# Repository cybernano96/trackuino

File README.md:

This is a modified version of "Trackuino": an open-source APRS tracker based on the Arduino platform. It was designed primarily to track high altitude balloons, so it has other handy features like reading temperature sensors and a buzzer for acoustic location.

Trackuino is intended for use by licensed radio amateurs.

This modified version supports serial via SoftwareSerial and the DRA818V radio module

**Please note:** This project is a fork of Trackuino, they are the original creators of the code.

Features
========

 * Custom PCB
 * GPS: any NMEA GPS will work fine
 * Radio: DRA818V (500/1000 mW).
 * 1200 bauds AFSK using 8-bit PWM
 * Sends out standard APRS position messages (latitude, longitude, altitude, course, speed and time).
 * Internal/external temperature sensors (LM60) to read temperature in and outside the payload
 * Active/passive buzzer support to ease acoustic payload location.
 * 1 x SMA female plugs (radio out)
 * Open source (GPLv2 license), both software and hardware. In other words, do whatever you want with it: modify it, add it to your project, etc. as long as you opensource your modifications as well.

Status
========

 * GPS ok!
 * DRA818V ok!
 * APRS AF OUT ok!
 * Buzzer ok!
 * Temp Sensor ok!

Download
========

The latest version is 1.52.

Use the `Download ZIP` button to get the source code.

Building
========

If you are building for the Arduino platform you need Arduino IDE version 1.8.13 or higher. Get it from the [Arduino web site](http://arduino.cc/).

Unzip the firmware in your sketches directory and load it up by double-clicking on trackuino.ino.

The single most important configuration file is "config.h". The file is self-documented. Here is where you set up your callsign, among other things.

Flashing
========

**Important**: When flashing the Arduino/Uno32, remove the Venus GPS or the entire Trackuino shield. After flashing the firmware, you can plug it back in. The GPS and the host computer share the same serial port on the AVR, so they will conflict when used together.

Hardware
========

The [Mini APRS Tracker](https://www.iu2frl.it/micro-aprs-tracker/) contains all the informations. PCB drawings coming soon!

Related projects
================

Some other HAB-related projects I wrote:

  * https://www.iu2frl.it/tracker-aprs-su-icom-ic-e2820/ - APRS Tracker for ICOM IC-2820
  * https://www.iu2frl.it/arduino-aprs-beacon/ - an APRS beacon
  * https://www.iu2frl.it/category/autocostruzione/aprs-autocostruzione/ - APRS related articles

Support
=======

Discuss firmware bugs or suggestions in the issue tracker.

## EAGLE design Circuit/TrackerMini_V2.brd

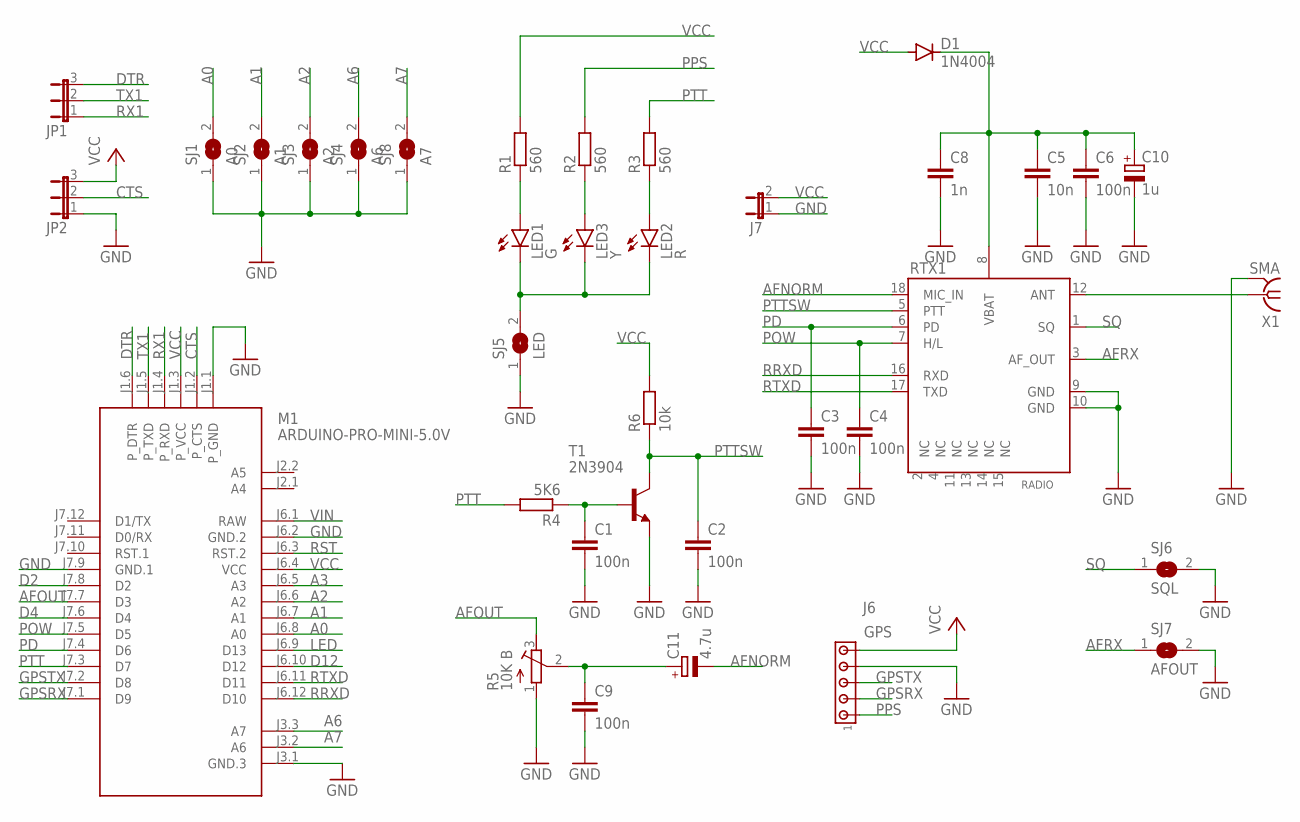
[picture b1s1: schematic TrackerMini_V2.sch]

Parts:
C1, C2, C3, C4, C6, C9: 100n; C025-025X050
C5: 10n; C025-025X050
C8: 1n; C025-025X050
C10: 1u; E2-5
C11: 4.7u; E2-5
D1: 1N4004; DO41-10
J6: GPS; 10X05MTA
J7: JP1E; JP1
JP1, JP2: JP2E; JP2
LED1: G; LED3MM
LED2: R; LED3MM
LED3: Y; LED3MM
M1: ARDUINO-PRO-MINI-5.0V; ARDUINO-PRO-MINI
R1, R2, R3: 560; 0204/7
R4: 5K6; 0204/7
R5: 10K B; RTRIM64W
R6: 10k; 0204/7
RTX1: RADIO; DRA818A
SJ1: A0; SJ
SJ2: A1; SJ
SJ3: A2; SJ
SJ4: A6; SJ
SJ5: LED; SJ
SJ6: SQL; SJW
SJ7: AFOUT; SJW
SJ8: A7; SJ
T1: 2N3904; TO92
X1: SMA; J502-ND-142-0701-801/806

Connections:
A0: M1.J6.8 (A0), SJ1.2
A1: M1.J6.7 (A1), SJ2.2
A2: M1.J6.6 (A2), SJ3.2
A3: M1.J6.5 (A3)
A6: M1.J3.3 (A7), SJ4.2
A7: M1.J3.2 (A6), SJ8.2
AFNORM: C11.-, RTX1.18 (MIC_IN)
AFOUT: M1.J7.7 (D3), R5.3 (E)
AFRX: RTX1.3 (AF_OUT), SJ7.1
CTS: JP2.2, M1.J1.2 (P_CTS)
D2: M1.J7.8 (D2)
D4: M1.J7.6 (D4)
D12: M1.J6.10 (D12)
DTR: JP1.3, M1.J1.6 (P_DTR)
GND: C1.2, C2.2, C3.2, C4.2, C5.2, C6.2, C8.2, C9.2, C10.-, J6.4, J7.1, JP2.1, M1.J1.1 (P_GND), M1.J3.1 (GND.3), M1.J6.2 (GND.2), M1.J7.9 (GND.1), R5.1 (A), RTX1.9 (GND), RTX1.10 (GND), SJ1.1, SJ2.1, SJ3.1, SJ4.1, SJ5.1, SJ6.2, SJ7.2, SJ8.1, T1.3 (E), X1.G@1 (2), X1.G@2 (2), X1.G@3 (2), X1.G@4 (2)
GPSRX: J6.2, M1.J7.1 (D9)
GPSTX: J6.3, M1.J7.2 (D8)
LED: M1.J6.9 (D13)
unnamed: LED1.A, R1.1
unnamed: LED3.A, R2.1
unnamed: LED2.A, R3.1
unnamed: LED1.K (C), LED2.K (C), LED3.K (C), SJ5.2
unnamed: RTX1.12 (ANT), X1.1
unnamed: C1.1, R4.1, T1.2 (B)
unnamed: C9.1, C11.+, R5.2 (S)
unnamed: C5.1, C6.1, C8.1, C10.+, D1.C, RTX1.8 (VBAT)
PD: C3.1, M1.J7.4 (D6), RTX1.6 (PD)
POW: C4.1, M1.J7.5 (D5), RTX1.7 (H/L)
PPS: J6.1, R2.2
PTT: M1.J7.3 (D7), R3.2, R4.2
PTTSW: C2.1, R6.1, RTX1.5 (PTT), T1.1 (C)
RRXD: M1.J6.12 (D10), RTX1.16 (RXD)
RST: M1.J6.3 (RST.2)
RTXD: M1.J6.11 (D11), RTX1.17 (TXD)
RX1: JP1.1, M1.J1.4 (P_RXD)
SQ: RTX1.1 (SQ), SJ6.1
TX1: JP1.2, M1.J1.5 (P_TXD)
VCC: D1.A, J6.5, J7.2, JP2.3, M1.J1.3 (P_VCC), M1.J6.4 (VCC), R1.2, R6.2
VIN: M1.J6.1 (RAW)

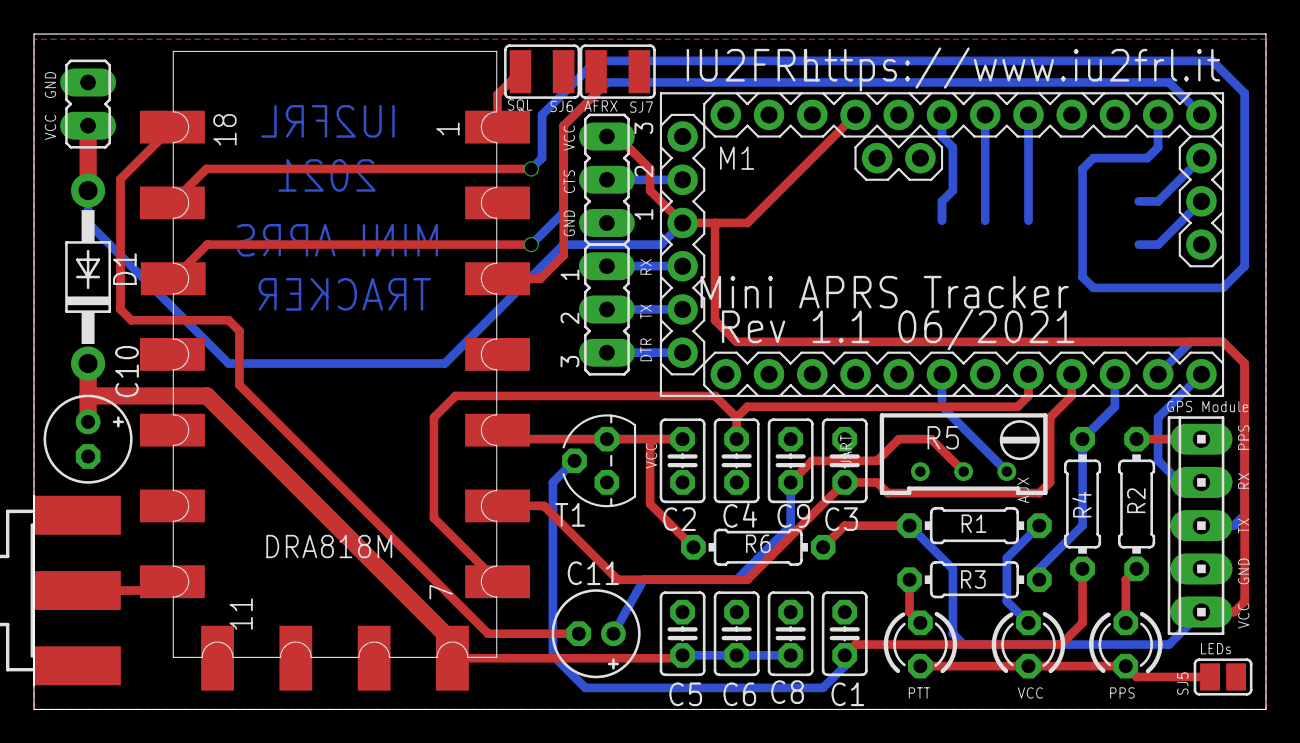
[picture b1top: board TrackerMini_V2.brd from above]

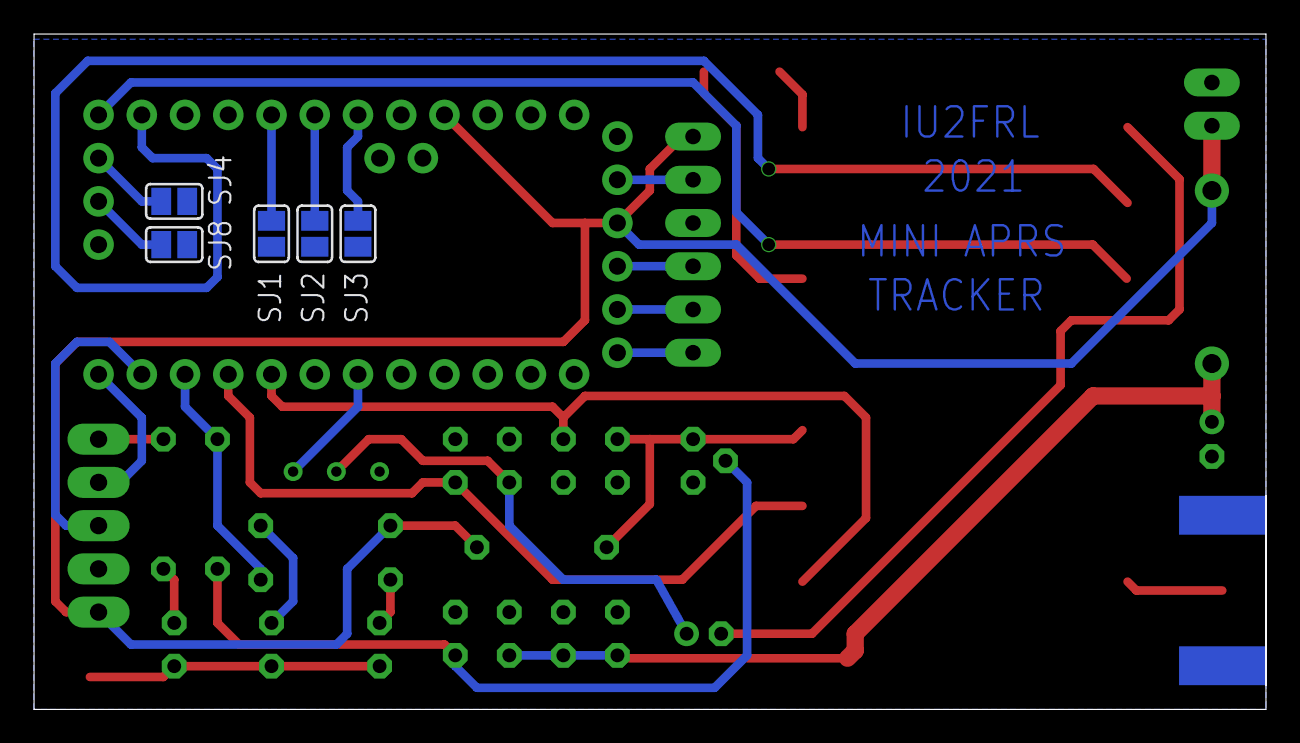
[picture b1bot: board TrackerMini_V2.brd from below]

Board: 2 copper layers, 72.4 x 39.7 mm, 36 parts (5 on the bottom side), 32 nets.

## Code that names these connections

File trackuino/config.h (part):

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// Radio config (radio_hx1.cpp)
// --------------------------------------------------------------------------

// This is the PTT pin
#define PTT_PIN           7
#define POW_PIN           5
#define RTXD              10
#define RRXD              11
#define RPD               6
#define RBAUD             9600
#define TXFREQ            144.800
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
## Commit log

2021-06-07 Added DRA818V module
2021-06-07 Copyright fix
2021-06-07 GPS via SoftwareSerial
2021-06-07 GPS no-fix comment first write
2021-06-08 Corretto interferenza con SoftwareSerial
2021-06-08 Configured sensors to be optional
2021-06-08 Aggiunti PCB
2021-11-28 Creazione cartelle separate
2023-02-19 No coordinates update bug fixed, GPS debugging disabled by default.
2023-02-21 Enclosure FreeCAD model and STLs added.

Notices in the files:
trackuino/config.h:
trackuino copyright (C) 2010  EA5HAV Javi
modify it under the terms of the GNU General Public License
parts and their libraries:
diy-modules: Released under the Creative Commons Attribution 4.0 International License: http://creativecommons.org/licenses/by/4.0
